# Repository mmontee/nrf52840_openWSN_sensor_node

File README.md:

<h1>nRF52840 OpenWSN Sensor Node</h1>

<ul>
  <li><a href="#project-overview">Project Overview</a>
    <ul>
      <li><a href="#current-software-status">Current Software Status</a></li>
      <li><a href="#current-hardware-status">Current Hardware Status</a></li>
    </ul>
  </li>
  <li><a href="#battery-life-analysis">Battery Life Analysis</a>
    <ul>
      <li><a href="#data-logger-node">Data Logger Node</a></li>
      <li><a href="#root-node">Root Node</a></li>
      <li><a href="#conclusion">Conclusion</a></li>
    </ul>
  </li>
  <li><a href="#guide-for-openwsn-on-xiao-nrf52840">Guide for OpenWSN on XIAO nRF52840</a>
    <ul>
      <li><a href="#uart-communication-with-openwsn-on-xiao-nrf52840">UART Communication with OpenWSN on XIAO nRF52840</a></li>
      <li><a href="#adc-driver-for-nrf52-saadc-xiao-nrf52840">ADC Driver for nRF52 SAADC (XIAO nRF52840)</a></li>
      <li><a href="#openwsn-adc-reader-application">OpenWSN ADC Reader Application</a></li>
    </ul>
  </li>
</ul>

<hr>

<h1 id="project-overview">Project Overview</h1>
<p>
This project builds upon the foundation of the <a href="https://github.com/mmontee/West_Lab_Hydrophone_Data_Logger">West_Lab_Hydrophone_Data_Logger</a>. The initial objective was to integrate the nRF52840 into the existing hardware architecture, with the long-term goal of migrating all signal processing tasks from the Teensy 4.0 to the nRF52840. This consolidation of processing onto a single microcontroller is expected to yield significant power savings while decreasing the complexity, size, and cost of each sensor node.
</p>
<p>
The ultimate aim is to create a wireless acoustic sensor network using the <a href="https://wiki.seeedstudio.com/XIAO_BLE/">XIAO nRF52840</a> and <a href="https://openwsn.org/">OpenWSN</a>. In the current transitional phase, a <a href="https://www.pjrc.com/store/teensy40.html">Teensy 4.0</a> with a <a href="https://www.pjrc.com/store/teensy3_audio.html">Teensy Audio Adaptor Board</a> captures and processes acoustic signals, and samples are saved to an SD card. The output is passed through the wireless network to a central root node. This root node does not perform sensing; instead, it passes information to an LTE-M modem, which uses MQTT to send the processed data to a cloud storage solution.
</p>
<p>
A critical aspect of the final transition will be to incorporate appropriate signal conditioning hardware to replace the functionality of the Teensy Audio Adaptor Board.
</p>

<h3 id="current-software-status">Current Software Status</h3>

<h4>Complete:</h4>
<ul>
  <li><strong>Hardware Programming</strong>: Established a method to program the device with OpenWSN.</li>
  <li><strong>Port OpenWSN to XIAO</strong>: Modified the existing OpenWSN project for the nRF52840-DK to support the XIAO.</li>
  <li><strong>Modified Openserial Driver</strong>: Adapted the openserial driver to enable UART communication between the Teensy and the nRF52840.</li>
  <li><strong>ADC Driver</strong>: Developed a dedicated ADC driver for the nRF52840's SAADC peripheral.</li>
  <li><strong>ADC Application</strong>: Created a sample application to demonstrate the driver's functionality and provide a foundation for future signal processing work.</li>
</ul>

<h4>Incomplete:</h4>
<ul>
  <li><strong>Signal Capture and Processing on nRF52840</strong>: Expand the ADC application to capture and process a time series of samples directly on the XIAO nRF52840.</li>
  <li><strong>Teensy 4.0 OpenWSN Output Parse Program</strong>: Procure a new LTE-M modem and continue testing/development.</li>
</ul>

<h3 id="current-hardware-status">Current Hardware Status</h3>
<h4>Complete:</h4>
<ul>
  <li>Each sensor node consists of a custom PCB that interfaces the XIAO nRF52840, Teensy boards, RTC battery, a battery management board, and various I/O.</li>
  <li>A root node adds an LTE-M modem in the form of a <a href="https://sequans.com/products/monarch-2-gm02sp-nektar-evk/">Sequans Communications Monarch 2 GM02SP Evaluation Kit</a>, which sends data to a central location.</li>
</ul>

<p align="center">
  
  <br>
  The existing West Lab Hydrophone Data Logger PCB.
</p>

<p align="center">
  
  <br>
  The existing West Lab Hydrophone Data Logger with an LTE-M modem.
</p>

<ul>
  <li>Shown below is the "West_Lab_Hydrophone_Data_Logger" PCB modified to include the XIAO nRF52840.</li>
</ul>

<h4>Incomplete:</h4>
<ul>
  <li>A new PCB revision that incorporates signal conditioning hardware and removes the Teensy 4.0 and its audio adapter board.</li>
</ul>

<h2 id="battery-life-analysis">Battery Life Analysis</h2>
 
<ul>
<li>This section uses average current consumption measurements made with a <a href="https://www.joulescope.com/">JouleScope</a> to estimate battery life.</li>
<li>Current consumption measurements were generated by attaching the JouleScope and allowing a device to run in a particular mode for over one minute. The resulting statistical average current consumption generated by the JouleScope software was recorded.</li>
</ul>

<h3 id="data-logger-node">Data Logger Node</h3>

<p align="center">
  
  <br>
  Battery life estimates for the data logger without the XIAO nRF52840.
</p>

<p align="center">
  
  <br>
  Battery life estimates for the data logger with the XIAO nRF52840.
</p>

<p align="center">
  
  <br>
  Battery life estimates for a data logger with only the XIAO nRF52840 (Teensy 4.0 and Audio Adaptor Board removed).
</p>

<h3 id="root-node">Root Node</h3> 

<p align="center">
  
  <br>
  Battery life estimates for the root node without a Teensy 4.0.
</p>

<p align="center">
  
  <br>
  Battery life estimates for the root node with a Teensy 4.0.
</p>

<h3 id="conclusion">Conclusion</h3> 

<p>The integration of the XIAO nRF52840 wireless mote introduces a significant power cost, primarily during idle periods.</p>
<ul>
    <li><strong>Impact at Operational Duty Cycle:</strong> At the target operational duty cycle of 6.6%, adding the nRF52840 reduces the battery life from 33.4 days to 30.0 days. This <strong>loss of only 3.4 days</strong> is a reasonable trade-off for gaining wireless mesh networking capabilities.</li>
    <li><strong>Idle Power is Key:</strong> The nRF52840's idle power consumption is its largest drawback. At a 0% duty cycle, its presence cuts the node's standby time by more than half, from 347 days to 149 days.</li>
    <li><strong>High-Duty Cycle Operation:</strong> As the data recording frequency increases, the power consumption of the Teensy processor becomes the dominant factor, and the relative impact of the nRF52840 diminishes.</li>
    <li><strong>Ultra-Low Power Potential:</strong> A simplified sensor node consisting of only the XIAO nRF52840 demonstrates the potential for extremely long-term deployments, lasting an estimated <strong>260 days</strong> on the same 10,000 mAh battery.</li>
</ul>ssss

<h4>Root Node: Designed for Function over Efficiency</h4>
<p>The Root Node hardware is configured for constant availability and processing power rather than battery longevity. Its battery life is extremely limited.</p>
<ul>
    <li><strong>Primary Power Drain:</strong> The largest power consumers are the always-on LTE modem and the Teensy processor. A base configuration with just the modem and nRF52840 lasts only <strong>5.8 days</strong>.</li>
    <li><strong>Teensy's High Cost:</strong> Adding the always-on Teensy for data processing is the single largest power draw, reducing the battery life by over 70% to just <strong>1.7 days</strong>.</li>
    <li><strong>Recommendations:</strong> For any practical deployment, the Root Node requires a continuous power source (e.g., mains or solar). Significant power savings could be achieved through future hardware and software revisions, such as implementing a sleep mode for the Teensy and power-cycling the LTE modem between scheduled transmissions.</li>
</ul>

<hr>

<h2 id="guide-for-openwsn-on-xiao-nrf52840">Guide for OpenWSN on XIAO nRF52840</h2>
<p>
Fortunately, foundational work has been completed in OpenWSN's nRF52840-DK implementation, which can be found in the <a href="https://github.com/openwsn-berkeley/openwsn-fw/tree/develop_FW-893">develop_FW-893 branch</a>. In this project, the <a href="https://www.nordicsemi.com/Products/Development-hardware/nRF52840-DK">nRF52840-DK</a> is used as a programmer and debugger for the XIAO nRF52840 board.
</p>
<p>
This guide will step through the processes of:
</p>
<ul>
  <li>Configuring the existing OpenWSN project for the XIAO nRF52840's pinout.</li>
  <li>Using the nRF52840-DK to program and debug the XIAO nRF52840.</li>
  <li>Using UART to transmit information to and from an OpenWSN application.</li>
</ul>

<p>This guide assumes you have the following hardware:</p>
<ul>
  <li>XIAO nRF52840 development board</li>
  <li>Nordic Semiconductor nRF52840-DK</li>
  <li><a href="https://wiki.seeedstudio.com/Seeeduino-XIAO-Expansion-Board/">Seeed Studio Expansion Base for XIAO</a> or the ability to solder jumper wires to the XIAO nRF52840.</li>
</ul>

<hr>

<h3>Software Setup</h3>
<ol>
  <li>
    <strong>Install Segger Embedded Studio for ARM (Legacy) V6.30.</strong><br>
    <a href="https://www.segger.com/downloads/embedded-studio/#ESforARM">https://www.segger.com/downloads/embedded-studio/#ESforARM</a>
    
  </li>
  <li>
    <strong>Clone the OpenWSN firmware repository:</strong><br>
    <code>git clone https://github.com/openwsn-berkeley/openwsn-fw</code>
  </li>
  <li>
    <strong>Switch to the correct branch:</strong><br>
    <code>git checkout develop_FW-893</code>
    
  </li>
  <li>
    <strong>Navigate to the project folder:</strong><br>
    <code>cd openwsn-fw/projects/nrf52840-DK/</code>
  </li>
  <li>
    <strong>Open the project file:</strong> <code>nrf52840_dk.emProject</code><br>
    The project should open in the Segger Embedded Studio IDE installed in the first step.
    
  </li>
</ol>

<hr>

<h3>Connecting the XIAO nRF52840 to the nRF52840-DK</h3>
<p>
Programming is done via the JTAG/SWD interface on the nRF52840-DK, which is exposed through the onboard J-Link debugger.
</p>
<ul>
  <li>Both boards must share a common ground reference.</li>
  <li>Power must be provided to both boards (in this guide, the nRF52840-DK powers the XIAO nRF52840).</li>
  <li>Connect SWD CLK.</li>
  <li>Connect SWD IO.</li>
  <li>Connect the jumper to enable the onboard debugger.</li>
</ul>
<p>The connections are illustrated below.</p>

<p>
We created the necessary connections using two methods:
</p>
<ol>
  <li>
    <strong>Using the "Expansion Board Base for XIAO":</strong> This board provides pogo pin contacts for the XIAO nRF52840's SWD pads, simplifying the connection process.
    
  </li>
  <li>
    <strong>Soldering wires directly:</strong> Alternatively, wire leads can be soldered to the XIAO nRF52840's SWD pads. The leads can then be connected directly to the nRF52840-DK as shown below.
    
  </li>
</ol>

<hr>

<h3>Modifying OpenWSN for the XIAO nRF52840</h3>
<p>Two changes must be made to the firmware to configure it for the XIAO nRF52840 platform: the UART and LED pin assignments must be updated.</p>
<ol>
  <li>
    The UART pin assignments are found in <code>bsp/uart.c</code>. The image below shows the correct values for the XIAO nRF52840.
    
  </li>
  <li>
    The LED pin assignments must be changed in <code>bsp/leds.c</code>. The image below shows the correct values for the XIAO nRF52840.
    
    Reference the schematic for LED pin assignments:
    
  </li>
</ol>

<hr>

<h3>Programming the XIAO nRF52840</h3>
<p>Assuming the necessary connections are established between the XIAO nRF52840 and the nRF52840-DK:</p>
<ol>
  <li>
    Set <code>03oos_openwsn</code> as the active project by right-clicking its name in the "Project Explorer".
    
  </li>
  <li>
    Compile the project: <strong>Build -> Build 03oos_openwsn</strong>.
    
  </li>
  <li>
    Program the device: <strong>Target -> Connect J-Link</strong>, then <strong>Target -> Download 03oos_openwsn</strong>.
    
  </li>
</ol>

<hr>

<h2 id="uart-communication-with-openwsn-on-xiao-nrf52840">Guide for UART Communication with OpenWSN on XIAO nRF52840</h2>
<p>
This project modifies <code>openserial.c</code> to execute functions when specific UART messages are received. Sensor nodes receive processed signal information from an external source (like the Teensy) and pass this data to the root node. The root node's UART output is then parsed by another device.
</p>
<p>
Incoming UART messages are parsed within <code>openserial.c</code> using a set of flags from <code>openhdlc.h</code> and command characters (<code>cmdByte</code>) defined in <code>openserial.h</code>, as shown below.
</p>
<p align="center">
  Flags<br>
  
</p>
<p align="center">
  cmdBytes<br>
  
</p>
<p>
Valid messages must be preceded by an <code>HDLC_FLAG</code>, begin with a valid command byte, contain the payload, and be terminated with a second <code>HDLC_FLAG</code>.
</p>
<p>
A message coming into openserial should have the form:<br>
<code>&lt;HDLC_FLAG&gt;&lt;cmdByte&gt;&lt;payload&gt;&lt;HDLC_FLAG&gt;</code>
</p>
<p>
We send information into the node using the following format, where <code>'~'</code> is the <code>HDLC_FLAG</code>, <code>'D'</code> is the <code>cmdByte</code>, and <code>'1234567890'</code> is example data:<br>
Example: <code>~D1234567890~</code>
</p>
<p>
After a valid message is parsed, it is passed to a switch statement that acts on the received <code>cmdByte</code>. This byte triggers a specific action. Below, the code passes the incoming data as that action or does nothing if the node is the root.
</p>

<p>
Once the data is on the data bus, it can be read by a custom application (e.g., `uinject`) that will create a UDP packet containing the data to be passed over the network.
</p>

<hr>

<h2 id="adc-driver-for-nrf52-saadc-xiao-nrf52840">ADC Driver for nRF52 SAADC (XIAO nRF52840)</h2>

<h3>1. Overview</h3>
<p>
This document describes a low-level driver for the nRF52 Successive-Approximation Analog-to-Digital Converter (SAADC) peripheral. The driver is designed for simplicity and provides a blocking (synchronous) API for single-channel ADC conversions.
</p>
<p>
It is specifically tailored with pin definitions corresponding to the analog pins on the <strong>Seeed Studio XIAO nRF52840</strong> board but can be adapted for other nRF52-based hardware.
</p>

<h4>Key Features</h4>
<ul>
  <li><strong>Easy Configuration</strong>: Uses a single configuration structure (<code>adc_config_t</code>) to set all major parameters.</li>
  <li><strong>Blocking Sampling</strong>: The <code>adc_sample()</code> function waits for the conversion to complete before returning, simplifying application logic.</li>
  <li><strong>Hardware Abstraction</strong>: Maps XIAO nRF52840 pin names (A0-A5) to the correct nRF52 AIN inputs.</li>
  <li><strong>Configurable Parameters</strong>:
    <ul>
      <li>Resolution (8, 10, 12, 14-bit)</li>
      <li>Hardware Oversampling (up to 256x)</li>
      <li>Reference Voltage (Internal 0.6V or VDD/4)</li>
      <li>Input Gain (1/6x to 4x)</li>
      <li>Acquisition Time (3µs to 40µs)</li>
    </ul>
  </li>
  <li><strong>Automatic Calibration</strong>: Performs an automatic offset calibration during initialization to improve accuracy.</li>
</ul>

<hr>

<h3>2. API Reference</h3>
<p>The driver exposes three main functions for controlling the ADC.</p>

<h4><code>void adc_init(const adc_config_t* config)</code></h4>
<p>
Initializes the SAADC peripheral with the specified settings. This function must be called before any sampling can occur.
</p>
<ul>
  <li><strong>Description</strong>: Configures the ADC resolution, oversampling, channel settings (pin, gain, reference, acquisition time), performs an offset calibration, and enables the peripheral.</li>
  <li><strong>Parameters</strong>:
    <ul>
      <li><code>config</code>: A pointer to a constant <code>adc_config_t</code> structure containing the desired ADC settings.</li>
    </ul>
  </li>
</ul>

<h4><code>bool adc_sample(uint16_t* result)</code></h4>
<p>Performs a single, blocking ADC conversion on the channel configured during initialization.</p>
<ul>
  <li><strong>Description</strong>: This function starts the ADC, triggers a sample, and waits for the <code>EVENTS_END</code> interrupt flag. It then copies the conversion result from the internal buffer to the user-provided location. To save power, it stops the ADC after the sample is complete.</li>
  <li><strong>Warning</strong>: This function blocks program execution until the conversion is complete.</li>
  <li><strong>Parameters</strong>:
    <ul>
      <li><code>result</code>: A pointer to a <code>uint16_t</code> variable where the ADC conversion result will be stored. The value's range depends on the configured resolution (e.g., 0-1023 for 10-bit).</li>
    </ul>
  </li>
  <li><strong>Returns</strong>:
    <ul>
      <li><code>true</code>: If the conversion was successful.</li>
      <li><code>false</code>: If the ADC was not initialized or the <code>result</code> pointer is NULL.</li>
    </ul>
  </li>
</ul>

<h4><code>void adc_uninit(void)</code></h4>
<p>Disables and powers down the SAADC peripheral to save energy.</p>
<ul>
  <li><strong>Description</strong>: Stops any ongoing conversions, disables the peripheral, and resets channel configurations. An <code>adc_init()</code> call is required before any new samples can be taken.</li>
</ul>

<hr>

<h3>3. Configuration</h3>
<p>Configuration is handled via the <code>adc_config_t</code> struct and several <code>enum</code> types.</p>

<h4><code>adc_config_t</code> Structure</h4>
<p>This structure holds all the necessary parameters for the <code>adc_init</code> function.</p>

<pre><code class="language-c">
typedef struct {
    adc_resolution_t       resolution;
    adc_oversample_t       oversample;
    adc_reference_t        reference;
    adc_gain_t             gain;
    adc_acqtime_t          acq_time;
    adc_analog_input_pin_t pin;
} adc_config_t;
</code></pre>

<h4>Configuration Enums</h4>

<h5><code>adc_analog_input_pin_t</code></h5>
<p>Selects the physical analog input pin on the XIAO nRF52840.</p>
<table>
  <thead>
    <tr>
      <th>Enum Value</th>
      <th>XIAO Pin</th>
      <th>nRF52 Pin</th>
      <th>nRF52 AIN</th>
    </tr>
  </thead>
  <tbody>
    <tr>
      <td><code>ADC_PIN_A0</code></td>
      <td>A0</td>
      <td>P0.02</td>
      <td>AIN0</td>
    </tr>
    <tr>
      <td><code>ADC_PIN_A1</code></td>
      <td>A1</td>
      <td>P0.03</td>
      <td>AIN1</td>
    </tr>
    <tr>
      <td><code>ADC_PIN_A2</code></td>
      <td>A2</td>
      <td>P0.28</td>
      <td>AIN4</td>
    </tr>
    <tr>
      <td><code>ADC_PIN_A3</code></td>
      <td>A3</td>
      <td>P0.29</td>
      <td>AIN5</td>
    </tr>
    <tr>
      <td><code>ADC_PIN_A4</code></td>
      <td>A4</td>
      <td>P0.04</td>
      <td>AIN2</td>
    </tr>
    <tr>
      <td><code>ADC_PIN_A5</code></td>
      <td>A5</td>
      <td>P0.05</td>
      <td>AIN3</td>
    </tr>
  </tbody>
</table>

<h5><code>adc_resolution_t</code></h5>
<p>Sets the bit resolution of the conversion. Higher resolution provides more precision but takes longer.</p>
<ul>
  <li><code>ADC_RESOLUTION_8BIT</code></li>
  <li><code>ADC_RESOLUTION_10BIT</code> (Common default)</li>
  <li><code>ADC_RESOLUTION_12BIT</code></li>
  <li><code>ADC_RESOLUTION_14BIT</code> (Requires acquisition time &ge; 10µs)</li>
</ul>

<h5><code>adc_oversample_t</code></h5>
<p>Enables hardware averaging to reduce noise. The ADC takes multiple samples and averages them into a single result.</p>
<ul>
  <li><code>ADC_OVERSAMPLE_DISABLED</code></li>
  <li><code>ADC_OVERSAMPLE_2X</code>, <code>_4X</code>, <code>_8X</code>, <code>_16X</code>, <code>_32X</code>, <code>_64X</code>, <code>_128X</code>, <code>_256X</code></li>
</ul>

<h5><code>adc_reference_t</code></h5>
<p>Selects the voltage reference for the conversion.</p>
<ul>
  <li><code>ADC_REFERENCE_INTERNAL</code>: Internal 0.6V reference.</li>
  <li><code>ADC_REFERENCE_VDD_DIV_4</code>: Uses VDD / 4 as the reference.</li>
</ul>

<h5><code>adc_gain_t</code></h5>
<p>Sets the gain for the internal pre-amplifier. The total input voltage range is determined by <code>V_Reference / Gain</code>.</p>
<table>
  <thead>
    <tr>
      <th>Enum Value</th>
      <th>Gain</th>
      <th>Input Range (with 0.6V VREF)</th>
      <th>Input Range (with VDD/4 VREF)</th>
    </tr>
  </thead>
  <tbody>
    <tr>
      <td><code>ADC_GAIN_1_6</code></td>
      <td>1/6x</td>
      <td>0 - 3.6V</td>
      <td>0 - 6.0V (e.g., if VDD=3.3V &rarr; 0-4.95V)</td>
    </tr>
    <tr>
      <td><code>ADC_GAIN_1_5</code></td>
      <td>1/5x</td>
      <td>0 - 3.0V</td>
      <td>0 - 5.0V (e.g., if VDD=3.3V &rarr; 0-4.125V)</td>
    </tr>
    <tr>
      <td><code>ADC_GAIN_1_4</code></td>
      <td>1/4x</td>
      <td>0 - 2.4V</td>
      <td>0 - 4.0V (e.g., if VDD=3.3V &rarr; 0-3.3V)</td>
    </tr>
    <tr>
      <td><code>ADC_GAIN_1_3</code></td>
      <td>1/3x</td>
      <td>0 - 1.8V</td>
      <td>0 - 3.0V (e.g., if VDD=3.3V &rarr; 0-2.475V)</td>
    </tr>
    <tr>
      <td><code>ADC_GAIN_1_2</code></td>
      <td>1/2x</td>
      <td>0 - 1.2V</td>
      <td>0 - 2.0V (e.g., if VDD=3.3V &rarr; 0-1.65V)</td>
    </tr>
    <tr>
      <td><code>ADC_GAIN_1</code></td>
      <td>1x</td>
      <td>0 - 0.6V</td>
      <td>0 - 1.0V (e.g., if VDD=3.3V &rarr; 0-0.825V)</td>
    </tr>
    <tr>
      <td><code>ADC_GAIN_2</code></td>
      <td>2x</td>
      <td>0 - 0.3V</td>
      <td>0 - 0.5V (e.g., if VDD=3.3V &rarr; 0-0.4125V)</td>
    </tr>
    <tr>
      <td><code>ADC_GAIN_4</code></td>
      <td>4x</td>
      <td>0 - 0.15V</td>
      <td>0 - 0.25V (e.g., if VDD=3.3V &rarr; 0-0.206V)</td>
    </tr>
  </tbody>
</table>
<p>
  <strong>Note:</strong> The actual input voltage range is limited by VDD. For example, with <code>ADC_GAIN_1_6</code> and VDD at 3.3V, the effective input range is 0V to 3.3V. <strong>The most common setting for measuring a voltage from 0 to VDD (e.g., 3.3V) is to use <code>ADC_REFERENCE_INTERNAL</code> and <code>ADC_GAIN_1_6</code>.</strong>
</p>

<h5><code>adc_acqtime_t</code></h5>
<p>Sets the acquisition time for the sample-and-hold capacitor. Longer times are needed for high-impedance sources.</p>
<ul>
  <li><code>ADC_ACQTIME_3US</code></li>
  <li><code>ADC_ACQTIME_5US</code></li>
  <li><code>ADC_ACQTIME_10US</code></li>
  <li><code>ADC_ACQTIME_15US</code></li>
  <li><code>ADC_ACQTIME_20US</code></li>
  <li><code>ADC_ACQTIME_40US</code></li>
</ul>

<hr>

<h3>4. Usage Example</h3>
<p>Here is a complete example of how to initialize, configure, and read from an analog pin.</p>

<pre><code class="language-c">
#include "adc.h"
#include &lt;stdio.h&gt; // For printing

int main(void) {
    // 1. Configure the ADC
    // This example configures the ADC to read a voltage between 0-3.6V
    // on pin A0 with 10-bit resolution.
    const adc_config_t my_adc_config = {
        .resolution = ADC_RESOLUTION_10BIT,
        .oversample = ADC_OVERSAMPLE_4X,      // Use 4x oversampling for better stability
        .reference  = ADC_REFERENCE_INTERNAL, // Use internal 0.6V reference
        .gain       = ADC_GAIN_1_6,           // Use 1/6 gain (effective input range is 0.6V * 6 = 3.6V)
        .acq_time   = ADC_ACQTIME_10US,
        .pin        = ADC_PIN_A0
    };

    // 2. Initialize the ADC
    adc_init(&my_adc_config);

    // 3. Main loop to sample the ADC
    while (1) {
        uint16_t adc_raw_value;

        // Take a sample
        if (adc_sample(&adc_raw_value)) {
            // Success! `adc_raw_value` contains the result (e.g., 0-1023 for 10-bit)

            // Optional: Convert raw value to millivolts
            // V_in_mV = (adc_raw_value / 1024.0) * 3600.0
            float voltage_mv = (float)adc_raw_value * (3600.0f / 1024.0f);

            // Print the result (assuming a UART or RTT is set up)
            printf("ADC Raw: %u, Voltage: %.2f mV\n", adc_raw_value, (double)voltage_mv);

        } else {
            // Handle error (e.g., ADC not initialized)
            printf("ADC sample failed.\n");
        }

        // Delay between samples
        for (volatile int i = 0; i < 1000000; i++);
    }

    // 4. Uninitialize (optional, typically not reached in a main loop)
    // adc_uninit();
}
</code></pre>

<hr>

<h1 id="openwsn-adc-reader-application">OpenWSN ADC Reader Application</h1>

<h3>1. Overview</h3>
<p>
This document describes <code>adcread</code>, a simple application component for the OpenWSN operating system. Its purpose is to periodically read an analog sensor using the <code>adc</code> driver and make the latest reading available to other parts of the system.
</p>
<p>
The application integrates with the OpenWSN kernel's <code>opentimers</code> service to schedule non-blocking, periodic ADC sampling. This makes it an efficient, low-power way to monitor a sensor.
</p>

<h4>Key Features</h4>
<ul>
  <li><strong>OpenWSN Integration</strong>: Built as a standard OpenWSN component that uses the kernel's timer service for scheduling.</li>
  <li><strong>Periodic Sampling</strong>: Automatically reads the configured ADC channel every 5 seconds (<code>ADC_READER_PERIOD_MS</code>).</li>
  <li><strong>Non-blocking API</strong>: Provides a simple, non-blocking function (<code>adcread_get_value()</code>) for other modules to retrieve the latest sensor data.</li>
  <li><strong>Power Efficient</strong>: The application is designed not to run on the DAGroot to save energy on the most critical node in the network.</li>
  <li><strong>Driver Abstraction</strong>: Uses the underlying <code>adc</code> peripheral driver, separating the application logic from the hardware-specific details.</li>
</ul>

<hr>

<h3>2. API Reference</h3>
<p>The <code>adcread</code> application exposes two public functions.</p>

<h4><code>void adcread_init(void)</code></h4>
<ul>
  <li><strong>Description</strong>: This function configures and initializes the underlying <code>adc</code> driver with static settings defined within <code>adcread.c</code>. It then creates and schedules a periodic timer that will trigger an ADC reading.</li>
  <li><strong>Warning</strong>: This function must be called <em>after</em> <code>opentimers_init()</code> has been successfully executed.</li>
</ul>

<h4><code>uint16_t adcread_get_value(void)</code></h4>
<ul>
  <li><strong>Description</strong>: This is a non-blocking function that immediately returns the most recent ADC value stored by the periodic timer task. It does not trigger a new ADC reading.</li>
  <li><strong>Returns</strong>: A <code>uint16_t</code> representing the latest raw ADC conversion result.</li>
</ul>

<hr>

<h3>3. Configuration</h3>
<p>
Unlike the driver, the application's configuration is hard-coded within the <code>adcread.c</code> file for simplicity. To change these settings, you must edit the source file and recompile.
</p>

<h4>Default ADC Configuration</h4>
<p>The following settings are applied in <code>adcread_init()</code>:</p>
<pre><code class="language-c">
// Statically defined configuration within adcread.c
adcread_vars.adc_config.resolution = ADC_RESOLUTION_12BIT;
adcread_vars.adc_config.oversample = ADC_OVERSAMPLE_DISABLED;
adcread_vars.adc_config.reference  = ADC_REFERENCE_INTERNAL; // 0.6V reference
adcread_vars.adc_config.gain       = ADC_GAIN_1_6;           // Input range = 0.6V / (1/6) = 3.6V
adcread_vars.adc_config.acq_time   = ADC_ACQTIME_10US;
adcread_vars.adc_config.pin        = ADC_PIN_A0;             // Reads from XIAO pin A0
</code></pre>

<h4>Sampling Period</h4>
<p>The sampling rate is controlled by a preprocessor macro:</p>
<pre><code class="language-c">
// Defines the period for reading the ADC in milliseconds
#define ADC_READER_PERIOD_MS 5000 // Read ADC every 5 seconds
</code></pre>

<hr>

<h3>4. Integration with OpenWSN</h3>
<p>Here is how to integrate and use the <code>adcread</code> application within the OpenWSN framework.</p>

<h4>1. Initialization</h4>
<p>
Call <code>adcread_init()</code> from the main system initialization function (e.g., in <code>openwsn.c</code>'s <code>openwsn_init</code> function), ensuring it is called after the kernel services are available.
</p>
<pre><code class="language-c">
// In openwsn.c or your main application file
#include "adcread.h"

void openwsn_init(void) {
    // ... other initializations
    board_init();
    scheduler_init();
    opentimers_init();
    // ... other initializations

    // Initialize the ADC reader application
    adcread_init();

    // ... more initializations
    scheduler_start();
}
</code></pre>

<h4>2. Retrieving Data</h4>
<p>
Other application modules (e.g., a data packet creation module like `C6T` or a custom application) can get the latest sensor data by calling <code>adcread_get_value()</code>.
</p>
<pre><code class="language-c">
// Example in another module that needs the sensor data
#include "adcread.h"

void send_sensor_data_task(void) {
    uint16_t sensor_value;

    // Get the latest value from the ADC reader app
    sensor_value = adcread_get_value();

    // Now, 'sensor_value' can be added to a packet payload
    // to be sent over the 6LoWPAN network.
    // ...
}
</code></pre>

<h4>3. Component ID</h4>
<p>
For error logging via <code>openserial_printLog</code>, ensure that <code>COMPONENT_ADCREAD</code> is defined in the <code>opendefs.h</code> file alongside other component IDs.
</p>

<hr>

<h3>5. Advanced Usage: Time-Series Sampling (Blocking Method)</h3>
<p>
For certain applications, you might need to capture a rapid burst of samples. The following method uses a <strong>blocking loop</strong> to monopolize the CPU and capture samples as fast as the hardware allows, without yielding control to the OpenWSN scheduler.
</p>

<p>
    Using a blocking loop in a cooperative OS like OpenWSN is dangerous and should be handled with extreme care.
</p>
<ul>
    <li><b>Processor Hogging</b>: The loop will prevent <b>all</b> other tasks from running, including the OpenWSN scheduler and the 6TiSCH network stack.</li>
    <li><b>Network Instability</b>: If the total time spent in the blocking loop is longer than a network timeslot (typically a few milliseconds), the node will fail to communicate. This can cause it to lose synchronization with the network, leading to packet loss or complete disconnection.</li>
    <li><b>When to Use</b>: This method is only acceptable for <strong>very short bursts</strong> where the total capture time is guaranteed to be minimal (e.g., less than one millisecond). For any longer duration, a non-blocking, task-based approach is required to maintain system stability.</li>
</ul>

<h4>Capturing a Burst with a Blocking Loop</h4>
<p>This is achieved by creating a function that enters a tight `for` loop, calling `adc_sample()` in each iteration.</p>

<p><strong>1. Define buffer and state variables:</strong><br>
First, define the buffer size in <code>adcread.c</code> and add necessary state variables to `adcread_vars_t`.</p>
<pre><code class="language-c">
// adcread.c
#define ADC_BURST_BUFFER_SIZE 256 // Capture 256 samples per burst

typedef struct {
    opentimers_id_t timer_id;
    uint16_t        latest_adc_value;
    adc_config_t    adc_config;
    bool            initialized;
    // --- New variables for burst mode ---
    uint16_t        burst_buffer[ADC_BURST_BUFFER_SIZE]; // Buffer for samples
    bool            burst_in_progress;                   // Flag to prevent re-entrant calls
} adcread_vars_t;
</code></pre>

<p><strong>2. Create the blocking capture function:</strong><br>
This function will contain the blocking loop. After the capture is complete, it schedules a separate, non-blocking task to process the data, which is a safer way to handle potentially long computations.</p>
<pre><code class="language-c">
// adcread.c -- function prototypes
void _adcread_process_task_cb(void); // Task to process data after capture
void adcread_capture_burst_blocking(void); // Public function to initiate a burst

// Public function with the blocking capture loop
void adcread_capture_burst_blocking(void) {
    if (!adcread_vars.initialized || adcread_vars.burst_in_progress) {
        return; // Exit if not ready or another burst is active
    }
    adcread_vars.burst_in_progress = true;

    // Stop the periodic timer to prevent interference
    opentimers_stop(adcread_vars.timer_id);

    // --- START OF BLOCKING SECTION ---
    // This loop takes full control of the CPU. No other tasks will run.
    for (uint16_t i = 0; i < ADC_BURST_BUFFER_SIZE; i++) {
        adc_sample(&adcread_vars.burst_buffer[i]);
    }
    // --- END OF BLOCKING SECTION ---

    // Now that the time-critical capture is done, schedule a
    // non-blocking task to process the data.
    scheduler_push_task(_adcread_process_task_cb, TASKPRIO_ADC);

    adcread_vars.burst_in_progress = false;

    // Restart the periodic timer for normal operation
    opentimers_scheduleIn(
        adcread_vars.timer_id,
        ADC_READER_PERIOD_MS,
        TIME_MS,
        TIMER_PERIODIC,
        _adcread_timer_cb
    );
}
</code></pre>

<h4>On-Mote Data Processing</h4>
<p>
Sending a large buffer of raw samples over the network is inefficient. Processing the data on the mote first and transmitting only the result reduces network traffic and saves energy. The `_adcread_process_task_cb` function is the ideal place for this computation, as it runs as a standard, non-blocking OpenWSN task.
</p>

<p><strong>Example Processing Task:</strong></p>
<pre><code class="language-c">
// adcread.c -- processing task
void _adcread_process_task_cb(void) {
    uint32_t sum = 0;
    uint16_t min_val = 0xFFFF;
    uint16_t max_val = 0x0000;

    // Iterate through the collected samples
    for (int i = 0; i < ADC_BURST_BUFFER_SIZE; i++) {
        uint16_t sample = adcread_vars.burst_buffer[i];
        sum += sample;

        if (sample < min_val) {
            min_val = sample;
        }
        if (sample > max_val) {
            max_val = sample;
        }
    }

    // Calculate the average
    uint16_t average_val = (uint16_t)(sum / ADC_BURST_BUFFER_SIZE);

    // Store the processed result in the main variable
    // This makes it available via the standard adcread_get_value() function
    adcread_vars.latest_adc_value = average_val;

    // For debugging, you could print the results
    // openserial_printf("Burst processed: Avg=%d, Min=%d, Max=%d\r\n", average_val, min_val, max_val);

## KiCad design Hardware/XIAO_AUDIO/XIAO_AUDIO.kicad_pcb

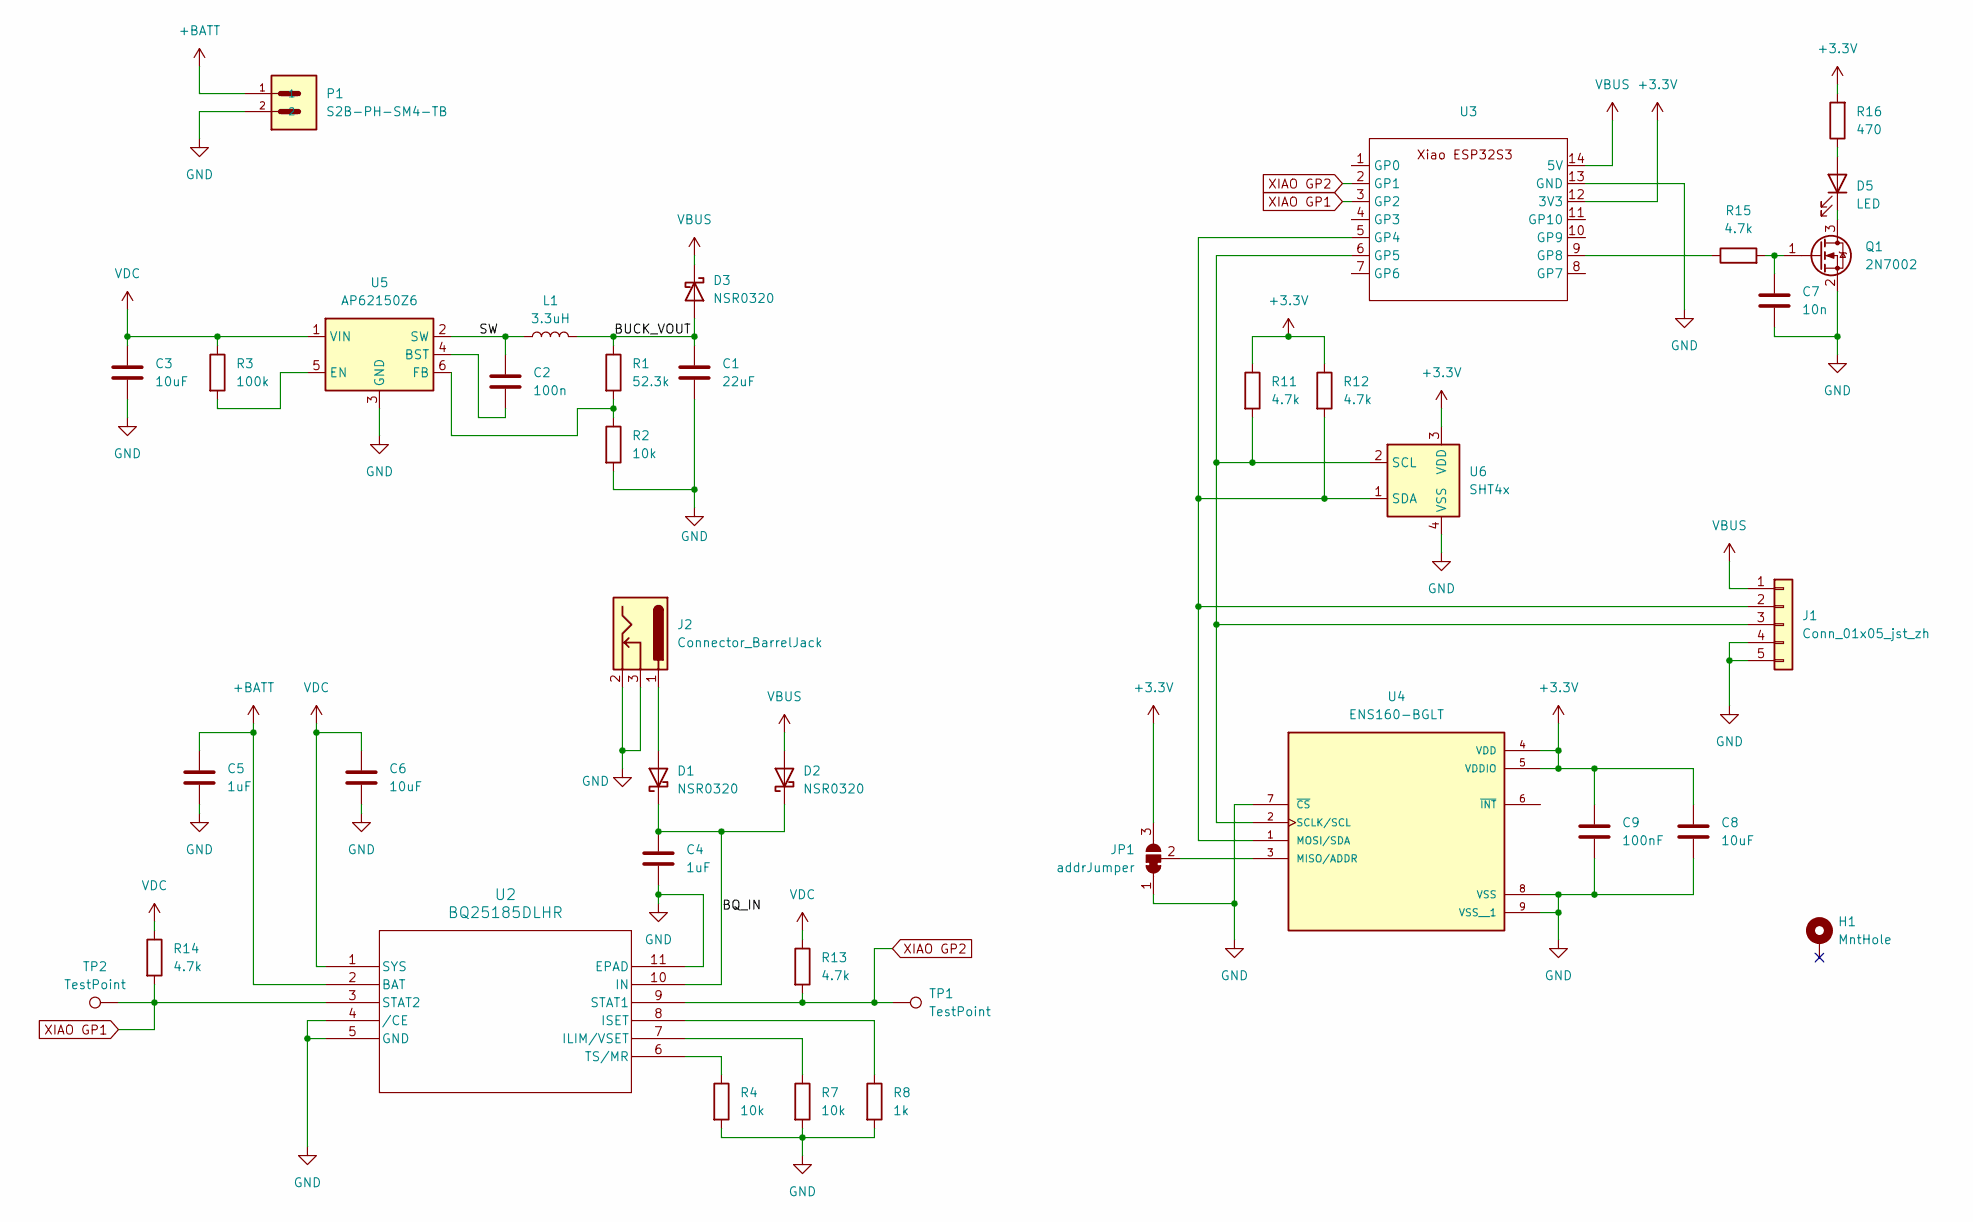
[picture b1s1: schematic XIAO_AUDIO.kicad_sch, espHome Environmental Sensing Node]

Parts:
C1: 22uF; C_0603_1608Metric_Pad1.08x0.95mm_HandSolder
C2: 100n; C_0603_1608Metric_Pad1.08x0.95mm_HandSolder
C3, C6, C8: 10uF; C_0603_1608Metric_Pad1.08x0.95mm_HandSolder
C4, C5: 1uF; C_0603_1608Metric_Pad1.08x0.95mm_HandSolder
C7: 10n; C_0603_1608Metric_Pad1.08x0.95mm_HandSolder
C9: 100nF; C_0603_1608Metric_Pad1.08x0.95mm_HandSolder
D1, D2, D3: NSR0320; D_SOD-323
D5: LED; LED_0603_1608Metric_Pad1.05x0.95mm_HandSolder
H1: MntHole; MountingHole_3mm_Pad_Via
J1: Conn_01x05_jst_zh; JST_ZH_B5B-ZR_1x05_P1.50mm_Vertical
J2: Connector_BarrelJack; BarrelJack_Wuerth_694102107102_1.0x3.9mm
JP1: addrJumper; SolderJumper-3_P1.3mm_Bridged12_RoundedPad1.0x1.5mm
L1: 3.3uH; NRS4018T3R3MDGJ
P1: S2B-PH-SM4-TB; JST_S2B-PH-SM4-TB
Q1: 2N7002; SOT-23
R1: 52.3k; R_0603_1608Metric_Pad0.98x0.95mm_HandSolder
R2, R4, R7: 10k; R_0603_1608Metric_Pad0.98x0.95mm_HandSolder
R3: 100k; R_0603_1608Metric_Pad0.98x0.95mm_HandSolder
R8: 1k; R_0603_1608Metric_Pad0.98x0.95mm_HandSolder
R11, R12, R13, R14, R15: 4.7k; R_0603_1608Metric_Pad0.98x0.95mm_HandSolder
R16: 470; R_0603_1608Metric_Pad0.98x0.95mm_HandSolder
TP1, TP2: TestPoint; TestPoint_Pad_D1.0mm
U2: BQ25185DLHR; WSON10_DLH_TEX
U3: XIAO_ESP32
U4: ENS160-BGLT; XDCR_ENS160-BGLT; PARTREV 1.3
U5: AP62150Z6; SOT-563
U6: SHT4x; Sensirion_DFN-4_1.5x1.5mm_P0.8mm_SHT4x_NoCentralPad

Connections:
+3.3V: C8.1, C9.1, JP1.3 (B), R11.1, R12.1, R16.2, U3.12 (3V3), U4.4 (VDD), U4.5 (VDDIO), U6.3 (VDD)
+BATT: C5.1, P1.1, U2.2 (BAT)
/BQ_IN: C4.1, D1.1 (K), D2.1 (K), U2.10 (IN)
/BUCK_VOUT: C1.1, D3.2 (A), L1.2, R1.1
/SW: C2.1, L1.1, U5.2 (SW)
GND: C1.2, C3.2, C4.2, C5.2, C6.2, C7.2, C8.2, C9.2, J1.4, J1.5, J2.2, J2.3, JP1.1 (A), P1.2, Q1.2 (S), R2.2, R4.2, R7.2, R8.2, U2.4 (/CE), U2.5 (GND), U2.11 (EPAD), U3.13 (GND), U4.7 (~CS), U4.8 (VSS), U4.9 (VSS__1), U5.3 (GND), U6.4 (VSS)
unnamed: D1.2 (A), J2.1
unnamed: D5.2 (A), R16.1
unnamed: D5.1 (K), Q1.3 (D)
unnamed: J1.2, R12.2, U3.5 (GP4), U4.1 (MOSI/SDA), U6.1 (SDA)
unnamed: J1.3, R11.2, U3.6 (GP5), U4.2 (SCLK/SCL), U6.2 (SCL)
unnamed: JP1.2 (C), U4.3 (MISO/ADDR)
unnamed: C7.1, Q1.1 (G), R15.2
unnamed: R7.1, U2.7 (ILIM/VSET)
unnamed: R8.1, U2.8 (ISET)
unnamed: R4.1, U2.6 (TS/MR)
unnamed: R15.1, U3.9 (GP8)
unnamed: C2.2, U5.4 (BST)
unnamed: R3.2, U5.5 (EN)
unnamed: R1.2, R2.1, U5.6 (FB)
VBUS: D2.2 (A), D3.1 (K), J1.1, U3.14 (5V)
VDC: C3.1, C6.1, R3.1, R13.1, R14.1, U2.1 (SYS), U5.1 (VIN)
XIAO GP1: R14.2, TP2.1, U2.3 (STAT2), U3.3 (GP2)
XIAO GP2: R13.2, TP1.1, U2.9 (STAT1), U3.2 (GP1)

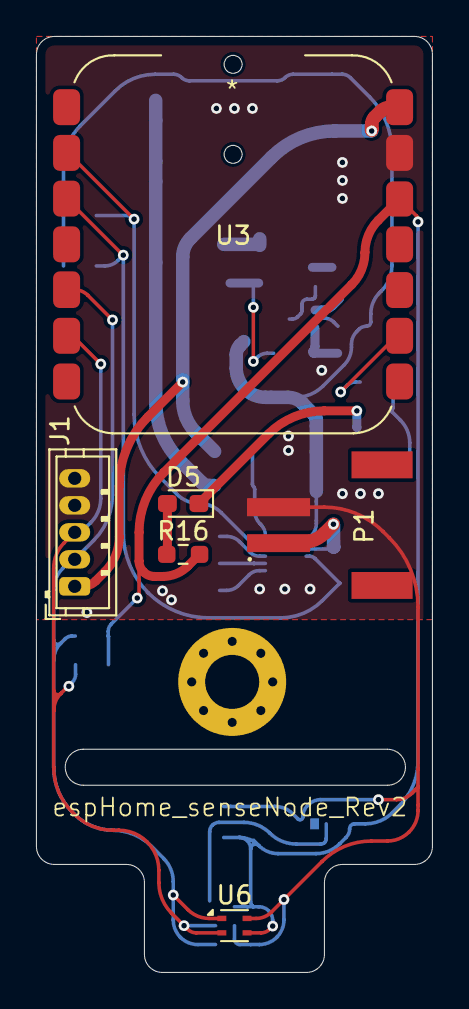
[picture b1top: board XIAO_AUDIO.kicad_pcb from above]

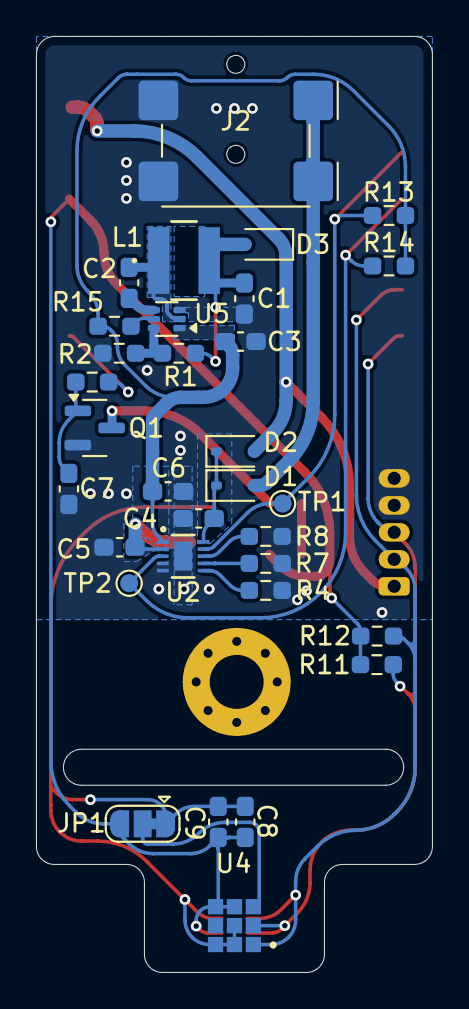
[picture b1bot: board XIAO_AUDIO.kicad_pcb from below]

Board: 2 copper layers, 22.0 x 52.0 mm, 39 parts (32 on the bottom side), 24 nets.

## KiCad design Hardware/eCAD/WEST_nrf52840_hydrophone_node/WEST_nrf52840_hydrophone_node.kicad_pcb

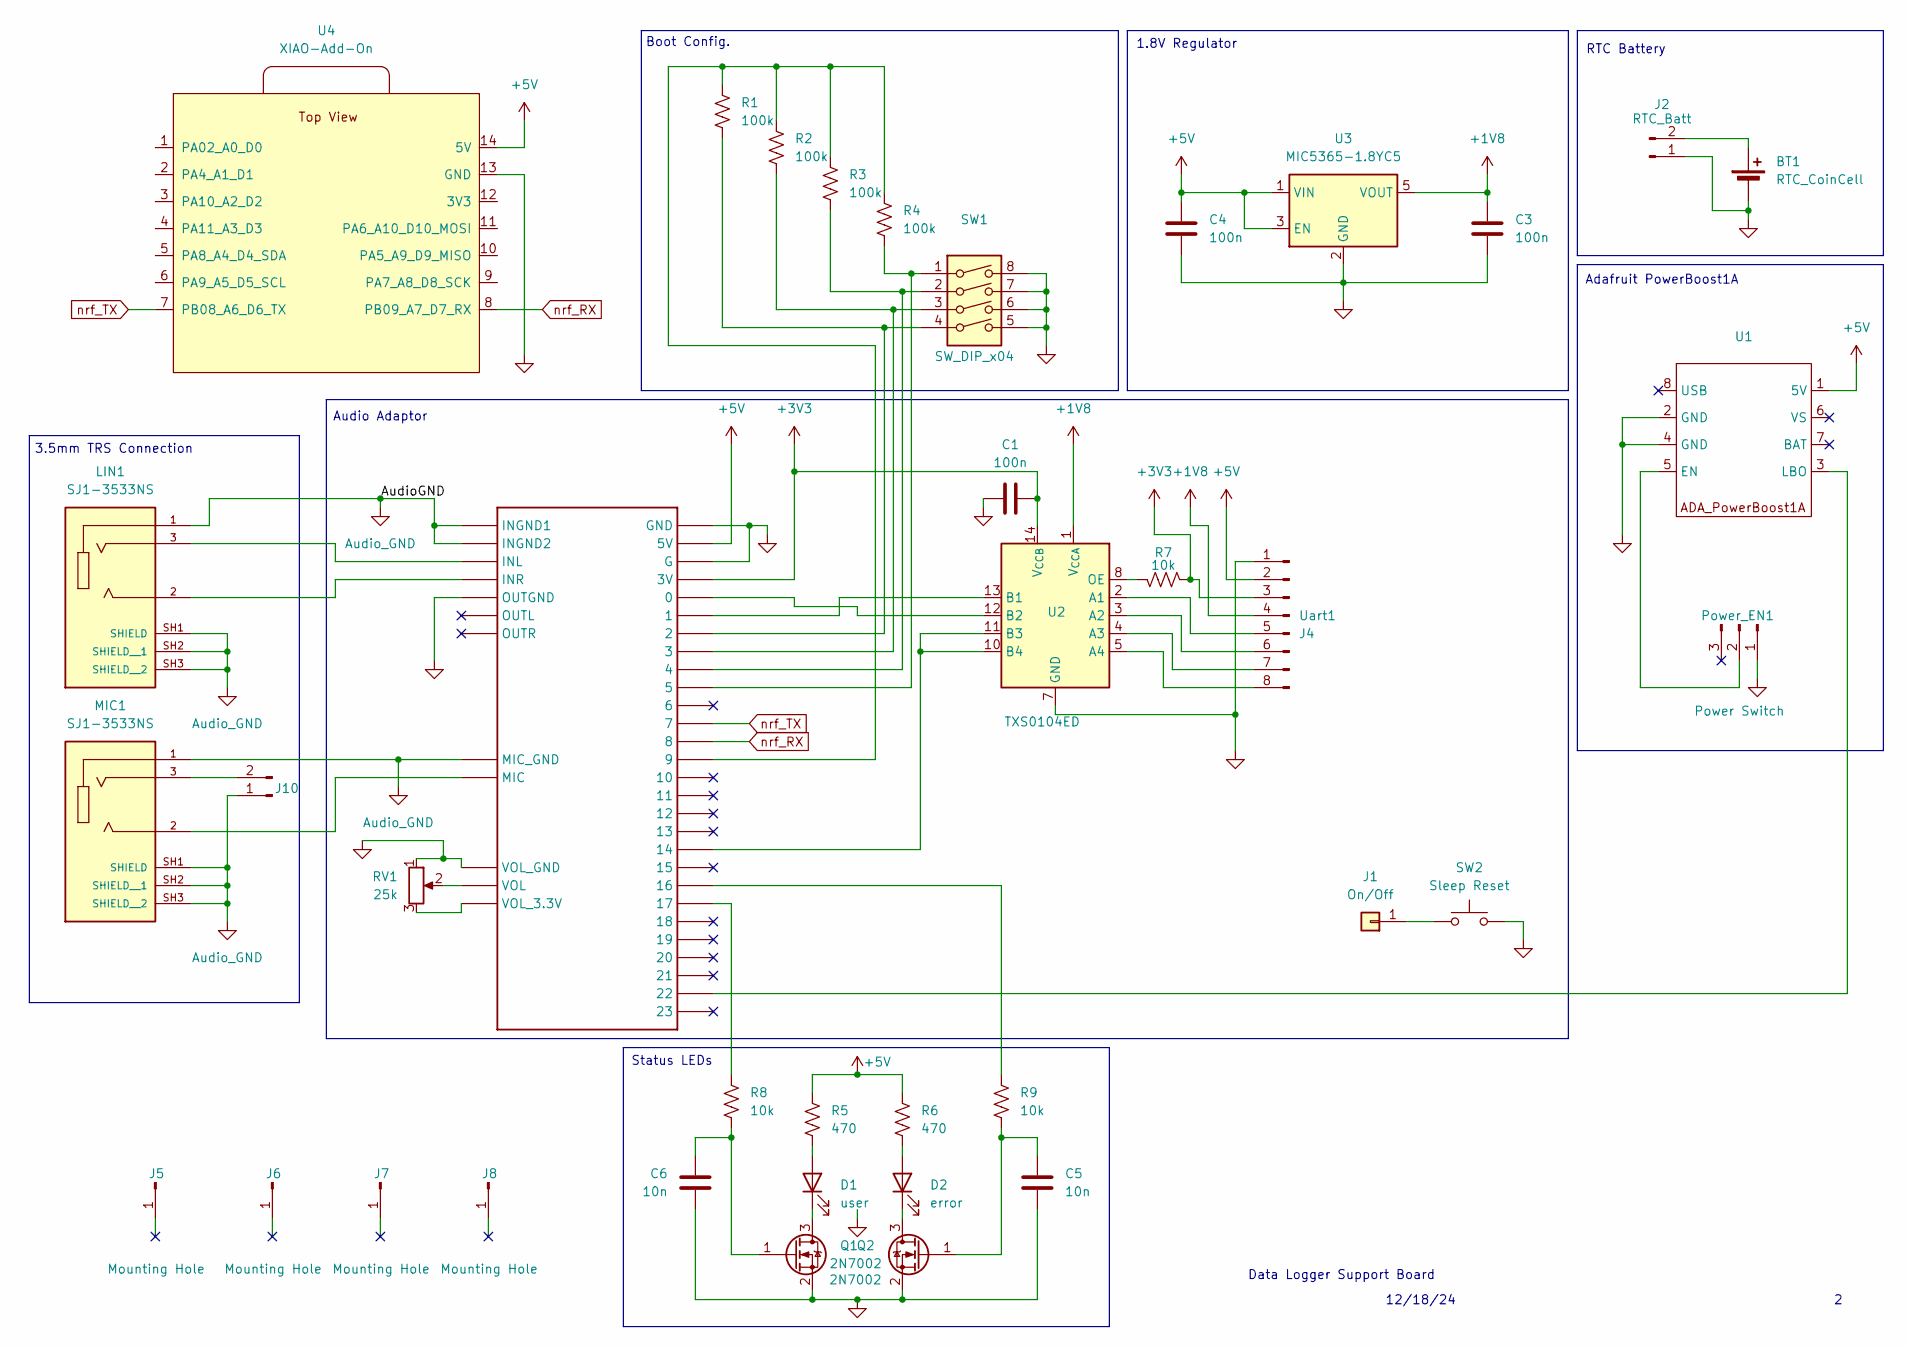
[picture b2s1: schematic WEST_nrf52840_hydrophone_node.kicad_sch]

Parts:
BT1: RTC_CoinCell; BatteryHolder_Keystone_3034_1x20mm
C1, C3, C4: 100n; C_0805_2012Metric_Pad1.18x1.45mm_HandSolder
C5, C6: 10n; C_0805_2012Metric_Pad1.18x1.45mm_HandSolder
D1: user; LED_0805_2012Metric_Pad1.15x1.40mm_HandSolder
D2: error; LED_0805_2012Metric_Pad1.15x1.40mm_HandSolder
J1: On/Off; PinSocket_1x01_P2.54mm_Vertical
J2: RTC_Batt; PinHeader_1x02_P2.54mm_Vertical
J4: Uart1
J5, J6, J7, J8: Mounting Hole; MountingHole_3.2mm_M3_Pad_Via
J10: Conn_01x02_Pin; SolderJumper-2_P1.3mm_Open_RoundedPad1.0x1.5mm
LIN1: SJ1-3533NS; CUI_SJ1-3533NS; PARTREV 1.04
MIC1: SJ1-3533NS; CUI_SJ1-3533NS; PARTREV 1.04
Power_EN1: Power Switch; SW_CK_JS202011CQN_DPDT_Straight
Q1, Q2: 2N7002; SOT-23
R1, R2, R3, R4: 100k; R_0805_2012Metric_Pad1.20x1.40mm_HandSolder
R5, R6: 470; R_0805_2012Metric_Pad1.20x1.40mm_HandSolder
R7, R8, R9: 10k; R_0805_2012Metric_Pad1.20x1.40mm_HandSolder
RV1: 25k
SW1: SW_DIP_x04; DIP8_208-4_CTS
SW2: Sleep Reset; SW_SPST_PTS647_Sx38
T1: AUDIOSHIELD
U1: ADA_powerBoost1A
U2: TXS0104ED; SOIC-14_3.9x8.7mm_P1.27mm
U3: MIC5365-1.8YC5; SOT-353_SC-70-5
U4: XIAO-Add-On; XIAO-nRF52840-DIP

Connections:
+1V8: C3.2, J4.4, U2.1 (V_{CCA}), U3.5 (VOUT)
+3V3: C1.2, J4.3, R7.1, T1.3V, U2.14 (V_{CCB})
+5V: C4.1, J4.2, R5.1, R6.1, T1.5V, U1.1 (5V), U3.1 (VIN), U3.3 (EN), U4.14 (5V); also elsewhere on the board
Audio_GND: J10.1, LIN1.1, LIN1.SH1 (SHIELD), LIN1.SH2 (SHIELD__1), LIN1.SH3 (SHIELD__2), MIC1.1, MIC1.SH1 (SHIELD), MIC1.SH2 (SHIELD__1), MIC1.SH3 (SHIELD__2), T1.GND_MIC (MIC_GND), T1.INGND1, T1.INGND2
GND: BT1.2 (-), C1.1, C3.1, C4.2, C5.1, C6.1, J2.1, J4.1, Power_EN1.1, Q1.2 (S), Q2.2 (S), RV1.1, SW1.5, SW1.6, SW1.7, SW1.8, SW2.2, T1.G, T1.GND, T1.OUTGND, T1.VOL_GND, U1.2 (GND), U1.4 (GND), U2.7 (GND), U3.2 (GND), U4.13 (GND); also elsewhere on the board
unnamed: BT1.1 (+), J2.2
unnamed: D1.2 (A), R5.2
unnamed: D1.1 (K), Q1.3 (D)
unnamed: D2.2 (A), R6.2
unnamed: D2.1 (K), Q2.3 (D)
unnamed: J1.1, SW2.1
unnamed 11: J4.5, U2.2 (A1); also elsewhere on the board
unnamed 12: J4.6, U2.3 (A2); also elsewhere on the board
unnamed 13: J4.7, U2.4 (A3); also elsewhere on the board
unnamed 14: J4.8, U2.5 (A4); also elsewhere on the board
unnamed: J10.2, MIC1.3
unnamed: LIN1.2, T1.INR
unnamed: LIN1.3, T1.INL
unnamed: MIC1.2, T1.MIC
unnamed: Power_EN1.2, U1.5 (EN)
unnamed: C6.2, Q1.1 (G), R8.2
unnamed: C5.2, Q2.1 (G), R9.2
unnamed: R1.1, R2.1, R3.1, R4.1, T1.9
unnamed: R1.2, SW1.4, T1.2
unnamed: R2.2, SW1.3, T1.3
unnamed: R3.2, SW1.2, T1.4
unnamed: R4.2, SW1.1, T1.5
unnamed: R8.1, T1.17
unnamed: R9.1, T1.16
unnamed: RV1.2, T1.VOL
unnamed: RV1.3, T1.VOL_3.3V
unnamed: T1.22, U1.3 (LBO)
unnamed: T1.1, U2.13 (B1)
unnamed: T1.0, U2.12 (B2)
unnamed: T1.14, U2.10 (B4), U2.11 (B3)
unnamed: R7.2, U2.8 (OE)
nrf_RX: T1.8, U4.8 (PB09_A7_D7_RX)
nrf_TX: T1.7, U4.7 (PB08_A6_D6_TX)

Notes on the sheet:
Status LEDs
3.5mm TRS Connection
12/18/24
Adafruit PowerBoost1A
RTC Battery
Audio Adaptor
Boot Config.
1.8V Regulator
Data Logger Support Board

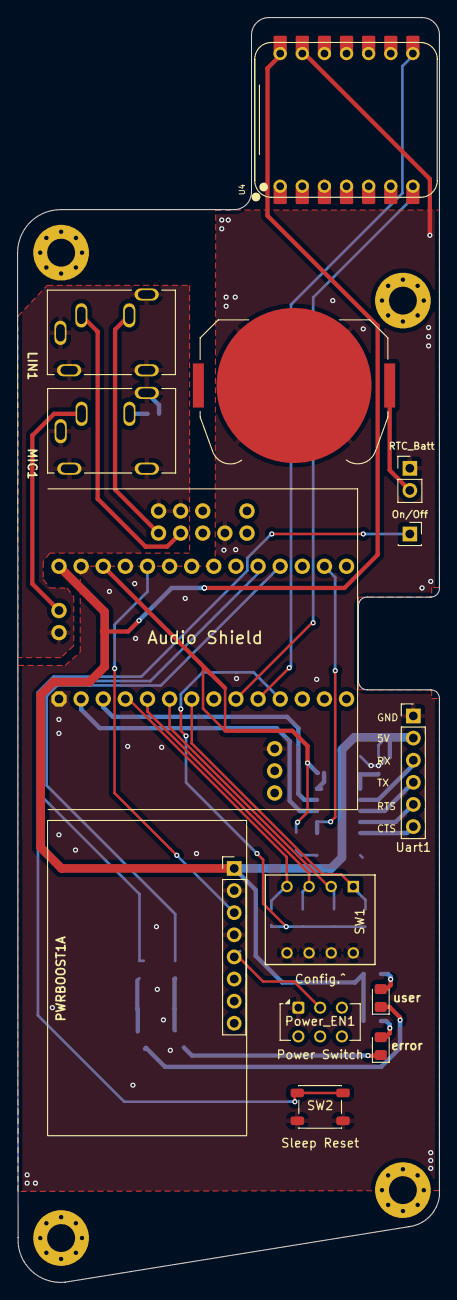
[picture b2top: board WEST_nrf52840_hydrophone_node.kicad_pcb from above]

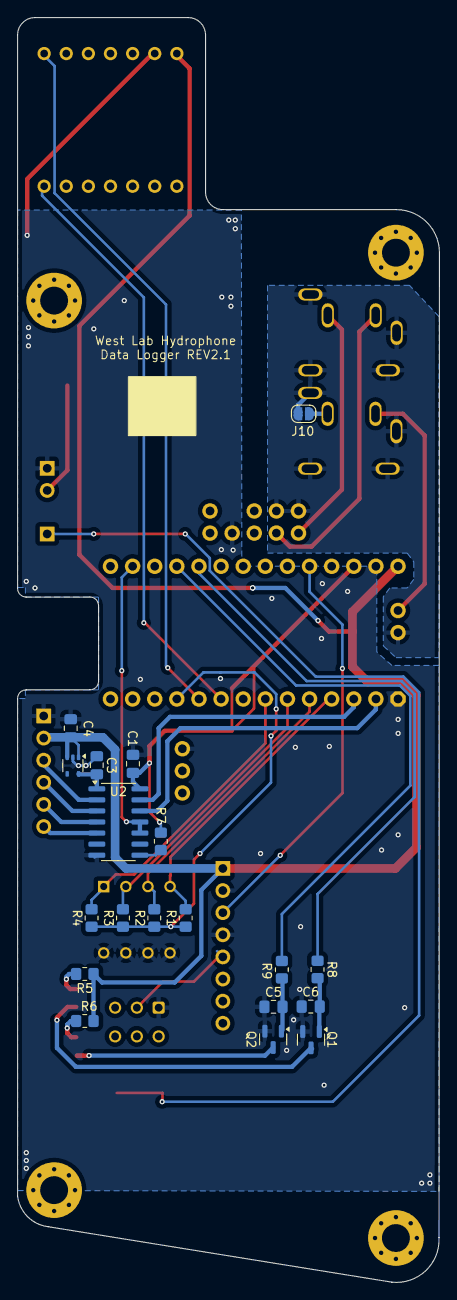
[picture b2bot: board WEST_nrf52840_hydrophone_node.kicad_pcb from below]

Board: 2 copper layers, 48.4 x 145.3 mm, 37 parts (19 on the bottom side), 36 nets.

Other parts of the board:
J3: Uart1; PinHeader_1x06_P2.54mm_Vertical

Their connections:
+5V: J3.2; also elsewhere on the board
GND: J3.1; also elsewhere on the board
unnamed 11: J3.3; also elsewhere on the board
unnamed 12: J3.4; also elsewhere on the board
unnamed 13: J3.5; also elsewhere on the board
unnamed 14: J3.6; also elsewhere on the board

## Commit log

2025-04-29 add openwsn-fw and openvisualizer as submodules. Add dev_log.
2025-04-29 remove berkely openwsn fork
2025-04-29 add my openwsn-fw fork. Add my changes to the develop_FW-893 branch
2025-05-23 readme update
2025-05-24 more readme work
2025-06-02 Readme updates, add kiCAD work, remove old sub-modules
2025-06-02 link openwsn-fw fork for XIAO as sub-module
2025-06-02 add Documents folder, readme updates
2025-06-05 chage of kiCAD project.
2025-06-06 Add plots notebook to docs
2025-06-06 Include python parse script
2025-06-09 adc driver/app info in readme
2025-06-10 Add battery life plots
2025-06-10 Update to battery life plot
2025-06-10 readme updates
2025-06-10 Expand readme
2025-06-10 updates to teensy-serial-reader
2025-06-10 battery analysis conclusion
2025-06-10 battery analysis conclusion expand
2025-09-15 Plot updtes
2025-09-19 pre demo checks
